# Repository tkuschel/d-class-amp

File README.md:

# d-class-amp

This electronic printed circuit board assembly (PCBA) is used in classes during electronics education. It is part of a Class-D amplifier.

## Educational Context

In the Electronics Engineering degree program, students complete the laboratory course **"PREL"** across the entire 3rd semester.
During this course, the hardware is developed and integrated step by step:

1. **Breadboard Prototype:** Students build a discrete Class-D amplifier on a breadboard, consisting of a microphone/input preamplifier, a tone control stage, a triangle wave generator, and a comparator.
2. **PCBA Integration:** This integrated printed circuit board assembly is then mounted onto the breadboard to replace or complement the discrete stages.
3. **Output Filter Design:** Finally, students dimension and assemble a 4-pole (4th-order) output low-pass filter on the breadboard before connecting the loudspeaker.

## Hardware & Documentation

* **Schematics & PCB Layout:** Located in the hardware design directories of this repository.
* **Lab Instructions:** Please refer to the course materials provided during the 3rd-semester PREL laboratory sessions.

## License

Copyright (c) 2026 Fachhochschule Technikum Wien (UAS Technikum Wien) / Thomas Kuschel

This hardware design is licensed under the **CERN Open Hardware Licence Version 2 - Weakly Reciprocal (CERN-OHL-W-2.0)**.
You may redistribute and modify this design and make products using it under the terms of the CERN-OHL-W-2.0.
See the [LICENSE](LICENSE) file for the full license text or visit the [official CERN OHL website](https://cern-ohl.web.cern.ch/).

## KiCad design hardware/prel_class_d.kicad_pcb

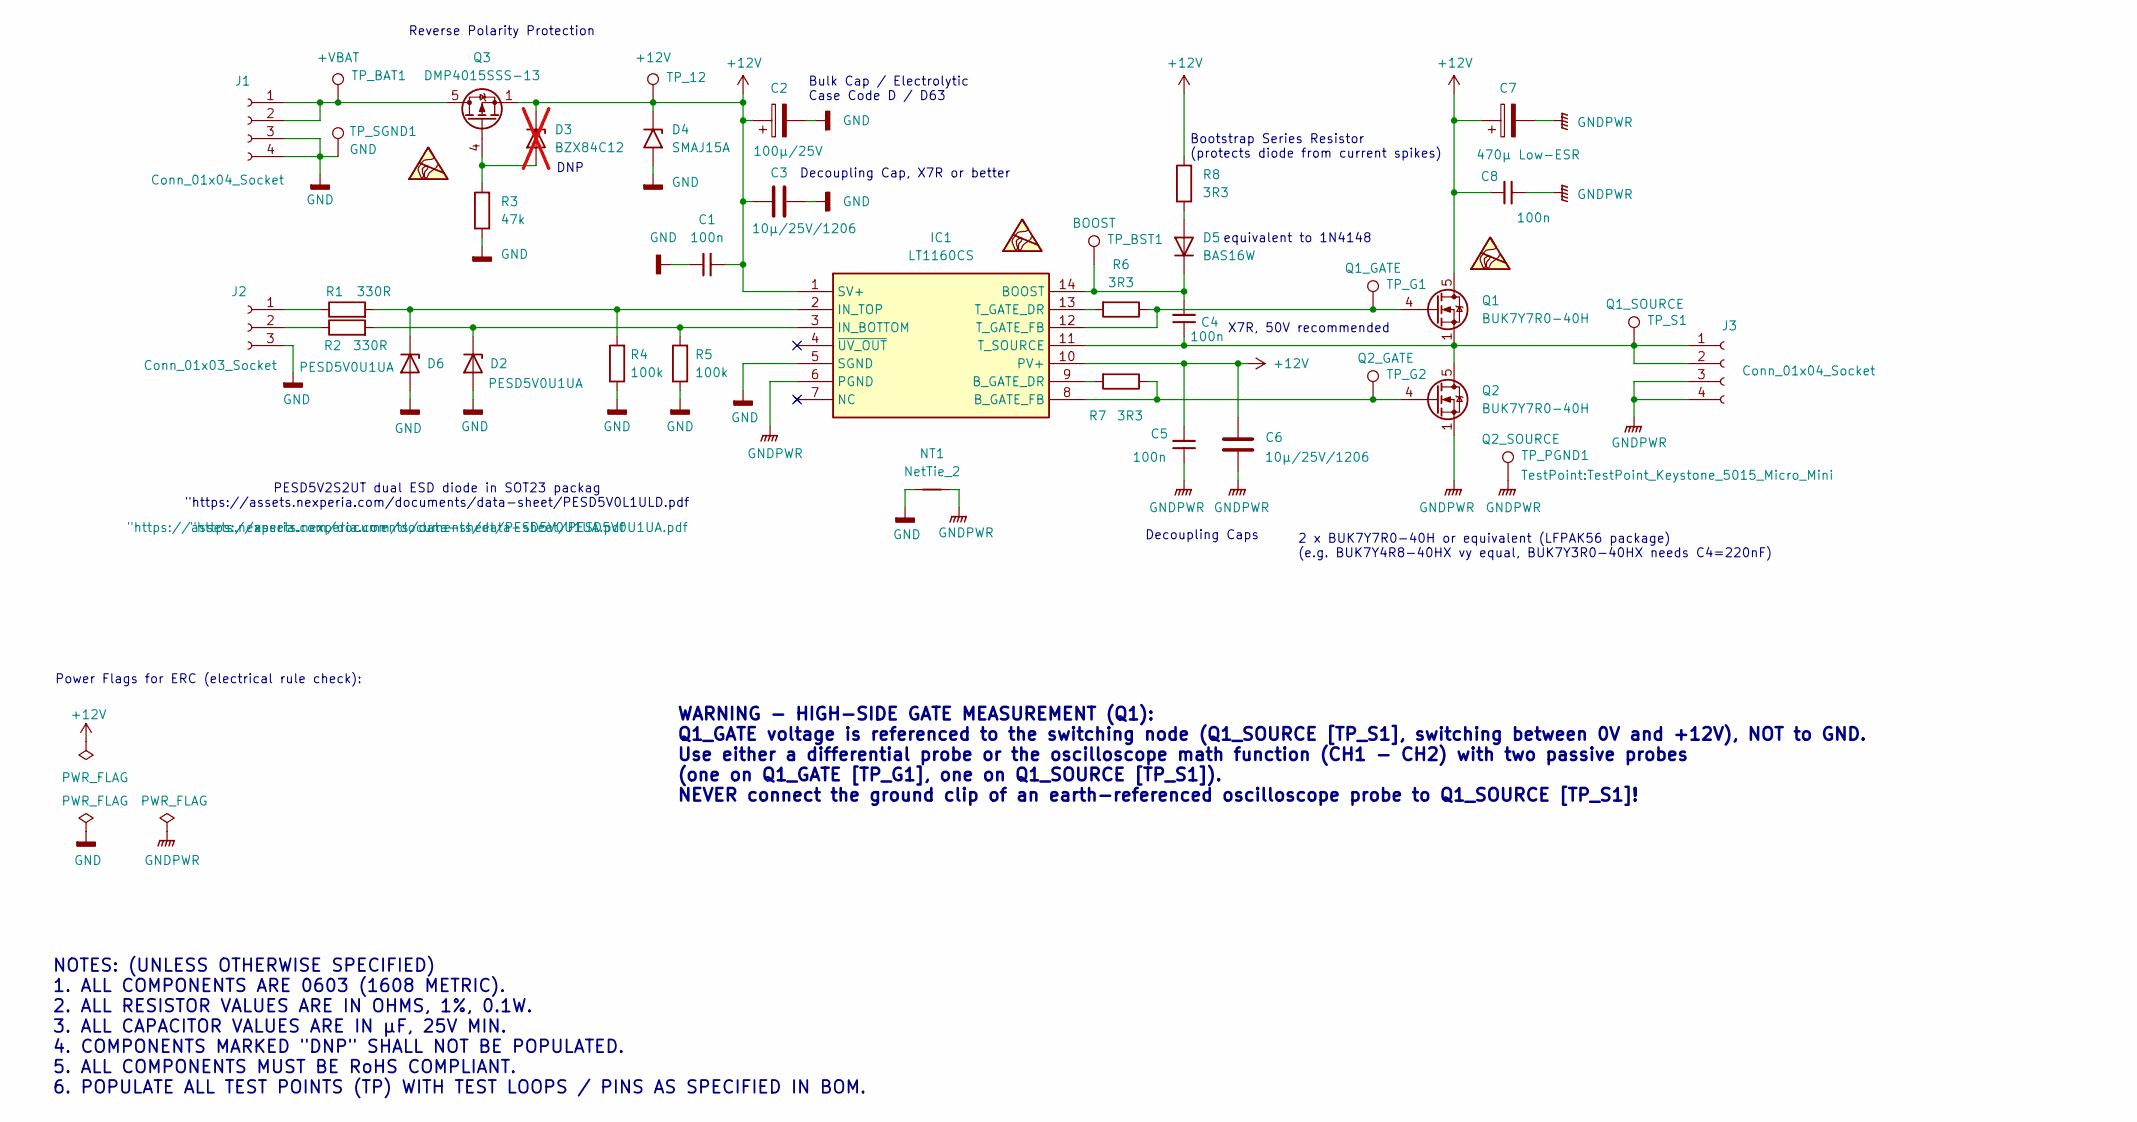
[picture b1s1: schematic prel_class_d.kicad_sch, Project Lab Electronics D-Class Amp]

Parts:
C1, C5, C8: 100n
C2: 100µ/25V
C3, C6: 10µ/25V/1206
C4: 100n; C_0603_1608Metric
C7: 470µ Low-ESR
D2, D6: PESD5V0U1UA; D_SOD-323
D3: BZX84C12; SOT-23; not fitted
D4: SMAJ15A; D_SMA
D5: BAS16W; SOT-323_SC-70
IC1: LT1160CS; SOIC-14_3.9x8.7mm_P1.27mm; Manufacturer_Part_Number LT1160CS#PBF; Mouser Part Number 584-LT1160CS#PBF
J1: Conn_01x04_Socket; PinSocket_1x04_P2.54mm_Vertical
J2: Conn_01x03_Socket
J3: Conn_01x04_Socket
NT1: NetTie_2
Q1, Q2: BUK7Y7R0-40H; LFPAK33
Q3: DMP4015SSS-13; SOIC-8_3.9x4.9mm_P1.27mm
R1, R2: 330R
R3: 47k
R4, R5: 100k
R6, R7, R8: 3R3
SYM1, SYM2, SYM3: SYM_ESD_Small; ESD-Logo_6.6x6mm_SilkScreen
TP_12: +12V
TP_BAT1: +VBAT
TP_BST1: BOOST
TP_G1: Q1_GATE
TP_G2: Q2_GATE
TP_PGND1: Q2_SOURCE; TestPoint_Keystone_5015_Micro_Mini
TP_S1: Q1_SOURCE
TP_SGND1: GND

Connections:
+12V: C1.2, C2.1, C3.2, C5.2, C6.1, C7.1, C8.2, D3.3 (K), D4.1 (A1), IC1.1 (SV+), IC1.10 (PV+), Q1.5 (D), Q3.1 (S), Q3.2 (S), Q3.3 (S), R8.2, TP_12.1 (1_1)
GND: C1.1, C2.2, C3.1, D2.2 (A), D4.2 (A2), D6.2 (A), IC1.5 (SGND), J1.3, J1.4, J2.3, NT1.1, R3.1, R4.1, R5.1, TP_SGND1.1 (1_1)
GNDPWR: C5.1, C6.2, C7.2, C8.1, IC1.6 (PGND), J3.3, J3.4, NT1.2, Q2.1 (S), Q2.2 (S), Q2.3 (S), TP_PGND1.1 (1_1)
unnamed: D2.1 (K), IC1.3 (IN_BOTTOM), R2.2, R5.2
unnamed: D3.1 (A), Q3.4 (G), R3.2
unnamed: D5.1 (A), R8.1
unnamed: C4.1, D5.3 (K), IC1.14 (BOOST), TP_BST1.1 (1_1)
unnamed: D6.1 (K), IC1.2 (IN_TOP), R1.2, R4.2
unnamed: IC1.9 (B_GATE_DR), R7.2
unnamed: IC1.8 (B_GATE_FB), Q2.4 (G), R7.1, TP_G2.1 (1_1)
unnamed: IC1.13 (T_GATE_DR), R6.2
unnamed: IC1.12 (T_GATE_FB), Q1.4 (G), R6.1, TP_G1.1 (1_1)
unnamed: C4.2, IC1.11 (T_SOURCE), J3.1, J3.2, Q1.1 (S), Q1.2 (S), Q1.3 (S), Q2.5 (D), TP_S1.1 (1_1)
unnamed: J1.1, J1.2, Q3.5 (D), Q3.6 (D), Q3.7 (D), Q3.8 (D), TP_BAT1.1 (1_1)
unnamed: J2.1, R1.1
unnamed: J2.2, R2.1

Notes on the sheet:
NOTES: (UNLESS OTHERWISE SPECIFIED) 1. ALL COMPONENTS ARE 0603 (1608 METRIC). 2. ALL RESISTOR VALUES ARE IN OHMS, 1%, 0.1W. 3. ALL CAPACITOR VALUES ARE IN µF, 25V MIN. 4. COMPONENTS MARKED "DNP" SHALL NOT BE POPULATED. 5. ALL COMPONENTS MUST BE RoHS COMPLIANT. 6. POPULATE ALL TEST POINTS (TP) WITH 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
Bootstrap Series Resistor (protects diode from current spikes)
DNP
PESD5V2S2UT dual ESD diode in SOT23 packag "https://assets.nexperia.com/documents/data-sheet/PESD5V0L1ULD.pdf
X7R, 50V recommended
equivalent to 1N4148
Decoupling Cap, X7R or better
WARNING - HIGH-SIDE GATE MEASUREMENT (Q1): Q1_GATE voltage is referenced to the switching node (Q1_SOURCE [TP_S1], switching between 0V and +12V), NOT to GND. Use either a differential probe or the oscilloscope math function (CH1 - CH2) with two passive probes (one on Q1_GATE [TP_G1], one on Q1_SOU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
Bulk Cap / Electrolytic Case Code D / D63
Decoupling Caps
Reverse Polarity Protection
Power Flags for ERC (electrical rule check):
2 x BUK7Y7R0-40H or equivalent (LFPAK56 package) (e.g. BUK7Y4R8-40HX vy equal, BUK7Y3R0-40HX needs C4=220nF)

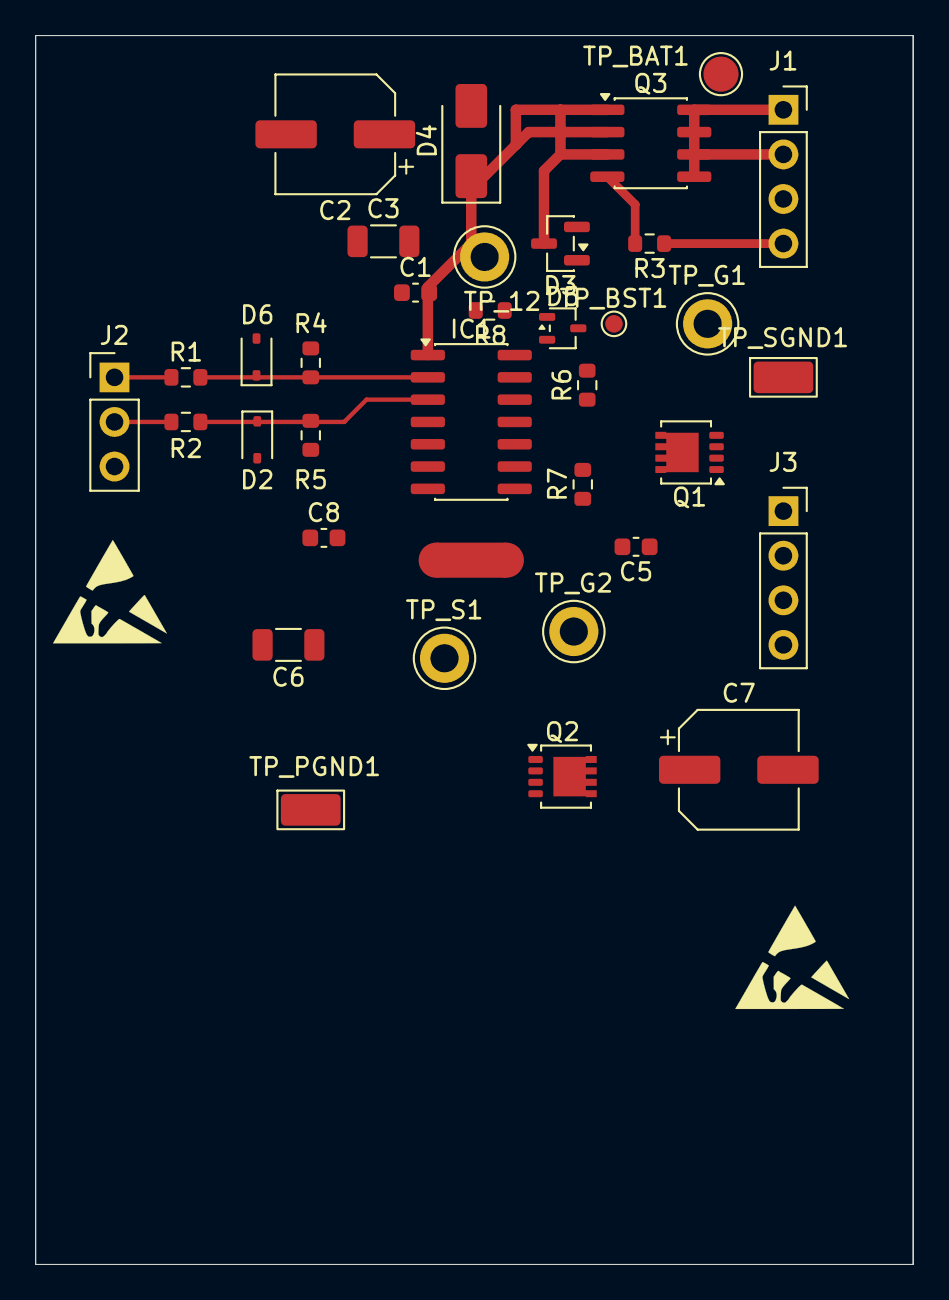
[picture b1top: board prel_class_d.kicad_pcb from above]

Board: 2 copper layers, 50.0 x 70.0 mm, 39 parts (1 on the bottom side), 16 nets.
